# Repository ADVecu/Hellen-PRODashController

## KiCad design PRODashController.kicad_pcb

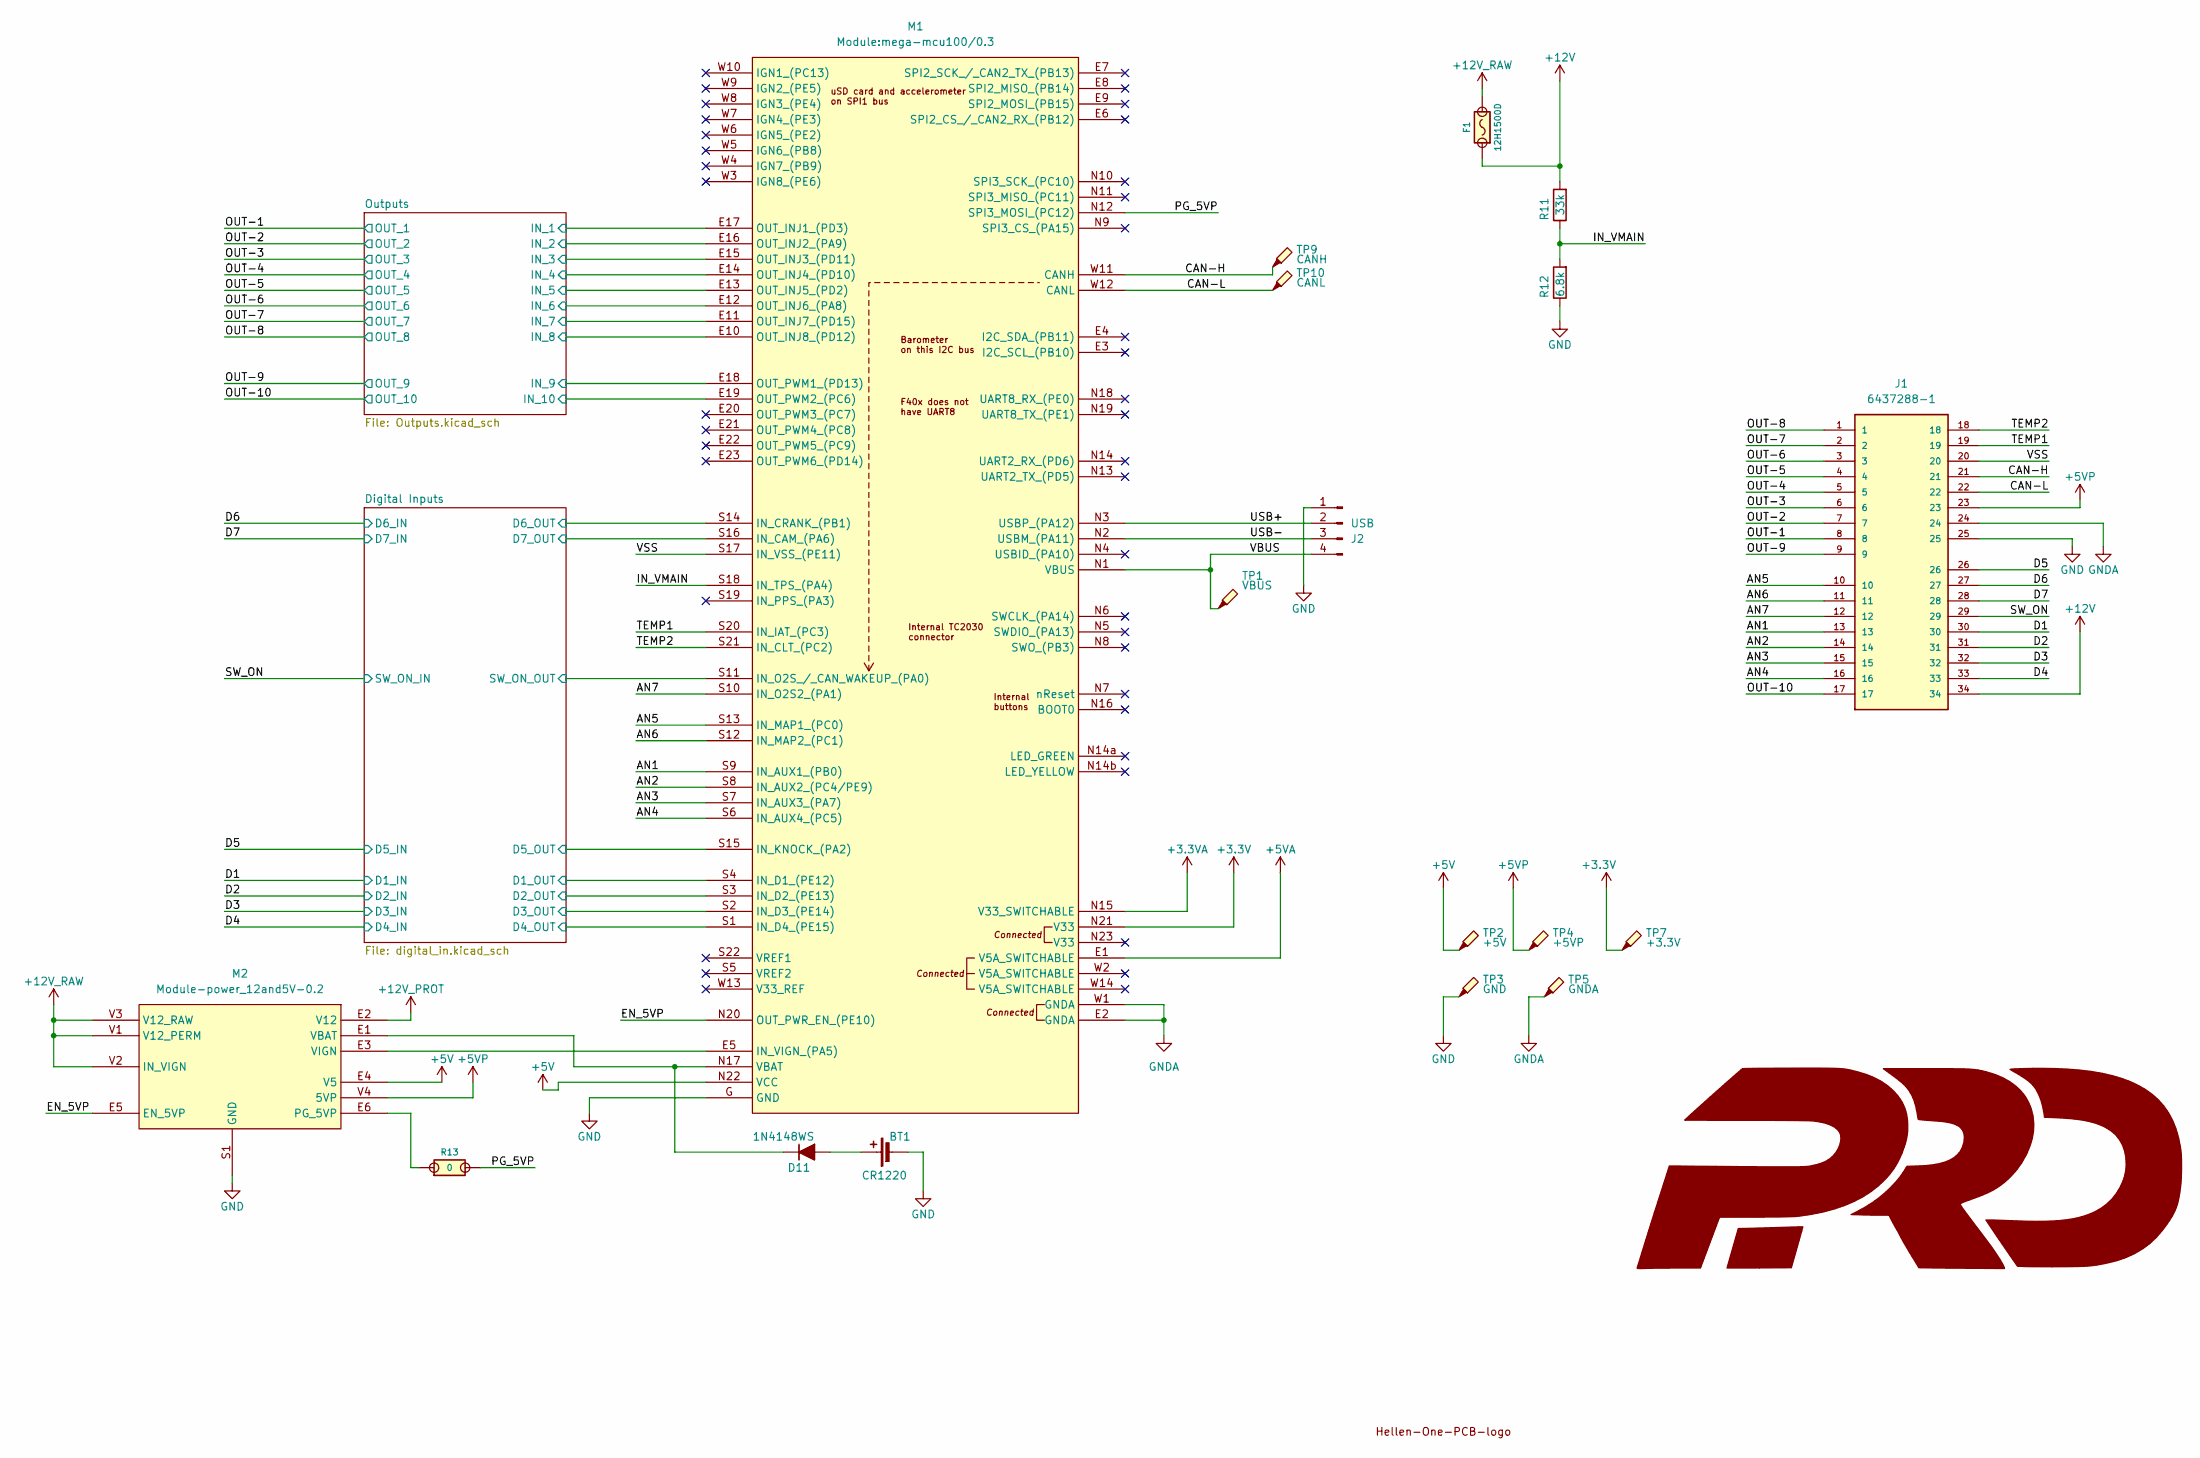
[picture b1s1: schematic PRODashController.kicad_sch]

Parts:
BT1: CR1220; CR1220-2; LCSC C70381
D11: 1N4148WS; SOD-323; LCSC C2128
F1: 12H1500D; PAD-1206-PAD; LCSC C182446
G1: LOGO
J1: 6437288-1; TE_6437288-1; PARTREV A1
J2: USB; JST_PH_B4B-PH-K_1x04_P2.00mm_Vertical; LCSC C5305780
M1: Module:mega-mcu100/0.3; mega-mcu100
M2: Module-power_12and5V-0.2; power_12and5V
R11: 33k; R0603; LCSC C4216
R12: 6.8k; R0603; LCSC C23212
R13: 0; R0805; LCSC C17477
TP1: VBUS; TestPoint_Pad_D1.0mm
TP2: +5V; TestPoint_Pad_D1.0mm
TP3: GND; TestPoint_Pad_D2.0mm
TP4: +5VP; TestPoint_Pad_D1.0mm
TP5: GNDA; TestPoint_Pad_D1.0mm
TP7: +3.3V; TestPoint_Pad_D1.0mm
TP9: CANH; TestPoint_Pad_D1.0mm
TP10: CANL; TestPoint_Pad_D1.0mm

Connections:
+3.3V: M1.N21 (V33), TP7.1
+3.3VA: M1.N15 (V33_SWITCHABLE)
+5V: M1.N22 (VCC), M2.E4 (V5), TP2.1
+5VA: M1.E1 (V5A_SWITCHABLE)
+5VP: J1.23, M2.V4 (5VP), TP4.1
+12V: F1.1, J1.34, R11.2
+12V_PROT: M2.E2 (V12); also elsewhere on the board
+12V_RAW: F1.2, M2.V1 (V12_PERM), M2.V2 (IN_VIGN), M2.V3 (V12_RAW); also elsewhere on the board
/AN1: J1.13, M1.S9 (IN_AUX1_(PB0))
/AN2: J1.14, M1.S8 (IN_AUX2_(PC4/PE9))
/AN3: J1.15, M1.S7 (IN_AUX3_(PA7))
/AN4: J1.16, M1.S6 (IN_AUX4_(PC5))
/AN5: J1.10, M1.S13 (IN_MAP1_(PC0))
/AN6: J1.11, M1.S12 (IN_MAP2_(PC1))
/AN7: J1.12, M1.S10 (IN_O2S2_(PA1))
/CAN-H: J1.21, M1.W11 (CANH), TP9.1
/CAN-L: J1.22, M1.W12 (CANL), TP10.1
/D1: J1.30; also elsewhere on the board
/D2: J1.31; also elsewhere on the board
/D3: J1.32; also elsewhere on the board
/D4: J1.33; also elsewhere on the board
/D5: J1.26; also elsewhere on the board
/D6: J1.27; also elsewhere on the board
/D7: J1.28; also elsewhere on the board
/Digital Inputs/D1_OUT: M1.S4 (IN_D1_(PE12)); also elsewhere on the board
/Digital Inputs/D2_OUT: M1.S3 (IN_D2_(PE13)); also elsewhere on the board
/Digital Inputs/D3_OUT: M1.S2 (IN_D3_(PE14)); also elsewhere on the board
/Digital Inputs/D4_OUT: M1.S1 (IN_D4_(PE15)); also elsewhere on the board
/Digital Inputs/D5_OUT: M1.S15 (IN_KNOCK_(PA2)); also elsewhere on the board
/Digital Inputs/D6_OUT: M1.S14 (IN_CRANK_(PB1)); also elsewhere on the board
/Digital Inputs/D7_OUT: M1.S16 (IN_CAM_(PA6)); also elsewhere on the board
/Digital Inputs/SW_ON_OUT: M1.S11 (IN_O2S_/_CAN_WAKEUP_(PA0)); also elsewhere on the board
/EN_5VP: M1.N20 (OUT_PWR_EN_(PE10)), M2.E5 (EN_5VP)
/IN_VMAIN: M1.S18 (IN_TPS_(PA4)), R11.1, R12.2
/OUT-1: J1.8; also elsewhere on the board
/OUT-2: J1.7; also elsewhere on the board
/OUT-3: J1.6; also elsewhere on the board
/OUT-4: J1.5; also elsewhere on the board
/OUT-5: J1.4; also elsewhere on the board
/OUT-6: J1.3; also elsewhere on the board
/OUT-7: J1.2; also elsewhere on the board
/OUT-8: J1.1; also elsewhere on the board
/OUT-9: J1.9; also elsewhere on the board
/OUT-10: J1.17; also elsewhere on the board
/Outputs/IN_1: M1.E17 (OUT_INJ1_(PD3)); also elsewhere on the board
/Outputs/IN_2: M1.E16 (OUT_INJ2_(PA9)); also elsewhere on the board
/Outputs/IN_3: M1.E15 (OUT_INJ3_(PD11)); also elsewhere on the board
/Outputs/IN_4: M1.E14 (OUT_INJ4_(PD10)); also elsewhere on the board
/Outputs/IN_5: M1.E13 (OUT_INJ5_(PD2)); also elsewhere on the board
/Outputs/IN_6: M1.E12 (OUT_INJ6_(PA8)); also elsewhere on the board
/Outputs/IN_7: M1.E11 (OUT_INJ7_(PD15)); also elsewhere on the board
/Outputs/IN_8: M1.E10 (OUT_INJ8_(PD12)); also elsewhere on the board
/Outputs/IN_9: M1.E18 (OUT_PWM1_(PD13)); also elsewhere on the board
/Outputs/IN_10: M1.E19 (OUT_PWM2_(PC6)); also elsewhere on the board
/PG_5VP: M1.N12 (SPI3_MOSI_(PC12)), R13.2
/SW_ON: J1.29; also elsewhere on the board
/TEMP1: J1.19, M1.S20 (IN_IAT_(PC3))
/TEMP2: J1.18, M1.S21 (IN_CLT_(PC2))
/USB+: J2.2, M1.N3 (USBP_(PA12))
/USB-: J2.3, M1.N2 (USBM_(PA11))
/VBUS: J2.4, M1.N1 (VBUS), TP1.1
/VSS: J1.20, M1.S17 (IN_VSS_(PE11))
GND: BT1.2 (-), J1.25, J2.1, M1.G (GND), M2.S1 (GND), R12.1, TP3.1; also elsewhere on the board
GNDA: J1.24, M1.E2 (GNDA), M1.W1 (GNDA), TP5.1
unnamed: BT1.1 (+), D11.2 (A)
unnamed: D11.1 (K), M1.N17 (VBAT), M2.E1 (VBAT)
unnamed: M1.E5 (IN_VIGN_(PA5)), M2.E3 (VIGN)
unnamed: M2.E6 (PG_5VP), R13.1

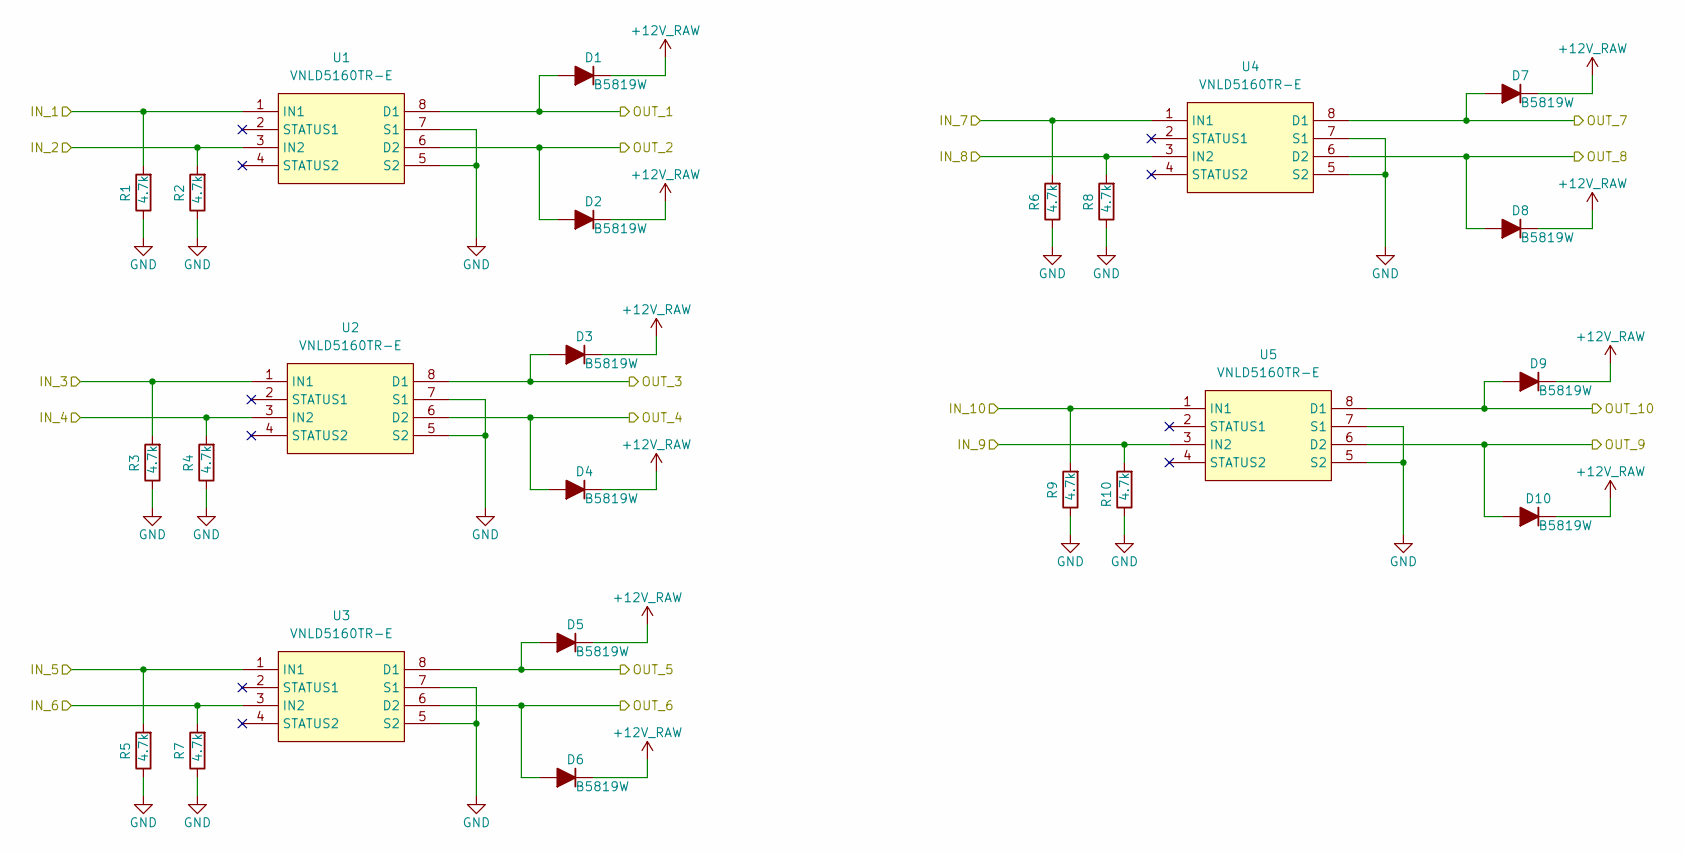
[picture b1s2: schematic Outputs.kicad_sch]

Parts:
D1, D2, D3, D4, D5, D6, D7, D8, D9, D10: B5819W; SOD-123; LCSC C8598
R1, R2, R3, R4, R5, R6, R7, R8, R9, R10: 4.7k; R0603; LCSC C23162
U1, U2, U3, U4, U5: VNLD5160TR-E; SOIC-8_3.9x4.9mm_P1.27mm; LCSC C377942

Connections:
+12V_RAW: D1.1 (K), D2.1 (K), D3.1 (K), D4.1 (K), D5.1 (K), D6.1 (K), D7.1 (K), D8.1 (K), D9.1 (K), D10.1 (K); also elsewhere on the board
/OUT-1: D1.2 (A), U1.8 (D1); also elsewhere on the board
/OUT-2: D2.2 (A), U1.6 (D2); also elsewhere on the board
/OUT-3: D3.2 (A), U2.8 (D1); also elsewhere on the board
/OUT-4: D4.2 (A), U2.6 (D2); also elsewhere on the board
/OUT-5: D5.2 (A), U3.8 (D1); also elsewhere on the board
/OUT-6: D6.2 (A), U3.6 (D2); also elsewhere on the board
/OUT-7: D7.2 (A), U4.8 (D1); also elsewhere on the board
/OUT-8: D8.2 (A), U4.6 (D2); also elsewhere on the board
/OUT-9: D10.2 (A), U5.6 (D2); also elsewhere on the board
/OUT-10: D9.2 (A), U5.8 (D1); also elsewhere on the board
/Outputs/IN_1: R1.2, U1.1 (IN1); also elsewhere on the board
/Outputs/IN_2: R2.2, U1.3 (IN2); also elsewhere on the board
/Outputs/IN_3: R3.2, U2.1 (IN1); also elsewhere on the board
/Outputs/IN_4: R4.2, U2.3 (IN2); also elsewhere on the board
/Outputs/IN_5: R5.2, U3.1 (IN1); also elsewhere on the board
/Outputs/IN_6: R7.2, U3.3 (IN2); also elsewhere on the board
/Outputs/IN_7: R6.2, U4.1 (IN1); also elsewhere on the board
/Outputs/IN_8: R8.2, U4.3 (IN2); also elsewhere on the board
/Outputs/IN_9: R10.2, U5.3 (IN2); also elsewhere on the board
/Outputs/IN_10: R9.2, U5.1 (IN1); also elsewhere on the board
GND: R1.1, R2.1, R3.1, R4.1, R5.1, R6.1, R7.1, R8.1, R9.1, R10.1, U1.5 (S2), U1.7 (S1), U2.5 (S2), U2.7 (S1), U3.5 (S2), U3.7 (S1), U4.5 (S2), U4.7 (S1), U5.5 (S2), U5.7 (S1); also elsewhere on the board

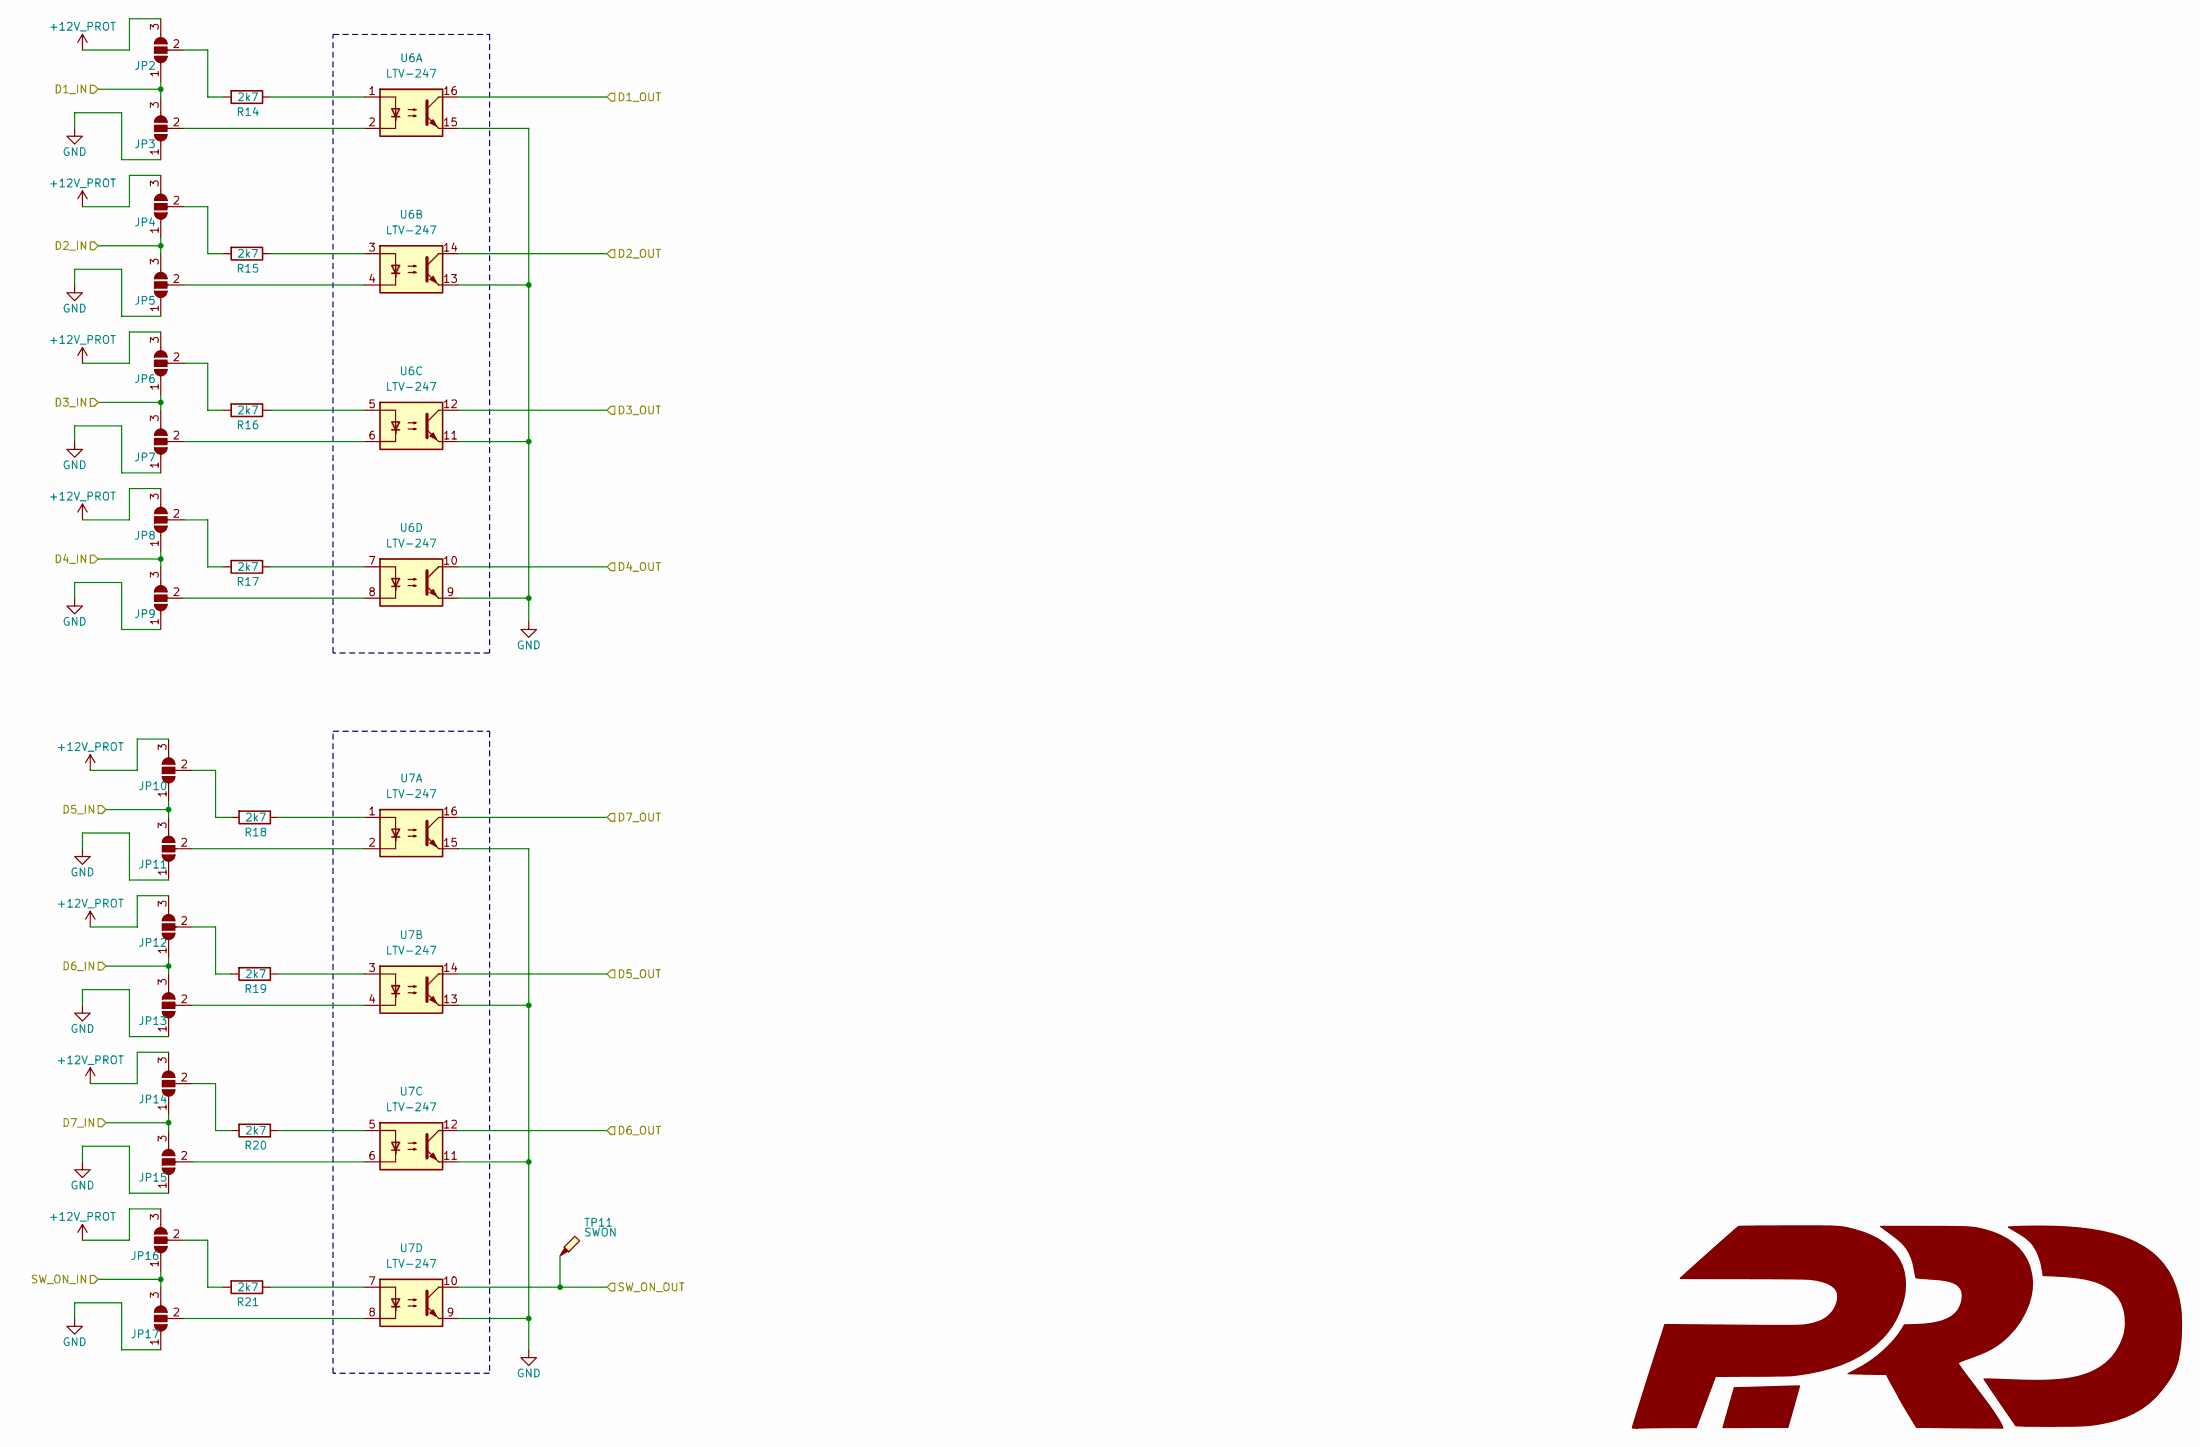
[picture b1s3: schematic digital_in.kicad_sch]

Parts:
JP2, JP3, JP4, JP5, JP6, JP7, JP8, JP9, JP10, JP11, JP12, JP13, JP14, JP15, JP16, JP17: SolderJumper_3_Open; SolderJumper-3_P1.3mm_Open_Pad1.0x1.5mm
R14, R15, R16, R17, R18, R19, R20, R21: 2k7; R0805; LCSC C17530
TP11: SWON; TestPoint_Pad_D1.0mm
U6, U7: LTV-247; SOP-16_4.4x10.4mm_P1.27mm; LCSC C115451

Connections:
+12V_PROT: JP2.3 (B), JP4.3 (B), JP6.3 (B), JP8.3 (B), JP10.3 (B), JP12.3 (B), JP14.3 (B), JP16.3 (B); also elsewhere on the board
/D1: JP2.1 (A), JP3.3 (B); also elsewhere on the board
/D2: JP4.1 (A), JP5.3 (B); also elsewhere on the board
/D3: JP6.1 (A), JP7.3 (B); also elsewhere on the board
/D4: JP8.1 (A), JP9.3 (B); also elsewhere on the board
/D5: JP10.1 (A), JP11.3 (B); also elsewhere on the board
/D6: JP12.1 (A), JP13.3 (B); also elsewhere on the board
/D7: JP14.1 (A), JP15.3 (B); also elsewhere on the board
/Digital Inputs/D1_OUT: U6.16; also elsewhere on the board
/Digital Inputs/D2_OUT: U6.14; also elsewhere on the board
/Digital Inputs/D3_OUT: U6.12; also elsewhere on the board
/Digital Inputs/D4_OUT: U6.10; also elsewhere on the board
/Digital Inputs/D5_OUT: U7.14; also elsewhere on the board
/Digital Inputs/D6_OUT: U7.12; also elsewhere on the board
/Digital Inputs/D7_OUT: U7.16; also elsewhere on the board
/Digital Inputs/SW_ON_OUT: TP11.1, U7.10; also elsewhere on the board
/SW_ON: JP16.1 (A), JP17.3 (B); also elsewhere on the board
GND: JP3.1 (A), JP5.1 (A), JP7.1 (A), JP9.1 (A), JP11.1 (A), JP13.1 (A), JP15.1 (A), JP17.1 (A), U6.9, U6.11, U6.13, U6.15, U7.9, U7.11, U7.13, U7.15; also elsewhere on the board
unnamed: JP2.2 (C), R14.2
unnamed: JP3.2 (C), U6.2
unnamed: JP4.2 (C), R15.2
unnamed: JP5.2 (C), U6.4
unnamed: JP6.2 (C), R16.2
unnamed: JP7.2 (C), U6.6
unnamed: JP8.2 (C), R17.2
unnamed: JP9.2 (C), U6.8
unnamed: JP10.2 (C), R18.2
unnamed: JP11.2 (C), U7.2
unnamed: JP12.2 (C), R19.2
unnamed: JP13.2 (C), U7.4
unnamed: JP14.2 (C), R20.2
unnamed: JP15.2 (C), U7.6
unnamed: JP16.2 (C), R21.2
unnamed: JP17.2 (C), U7.8
unnamed: R14.1, U6.1
unnamed: R15.1, U6.3
unnamed: R16.1, U6.5
unnamed: R17.1, U6.7
unnamed: R18.1, U7.1
unnamed: R19.1, U7.3
unnamed: R20.1, U7.5
unnamed: R21.1, U7.7

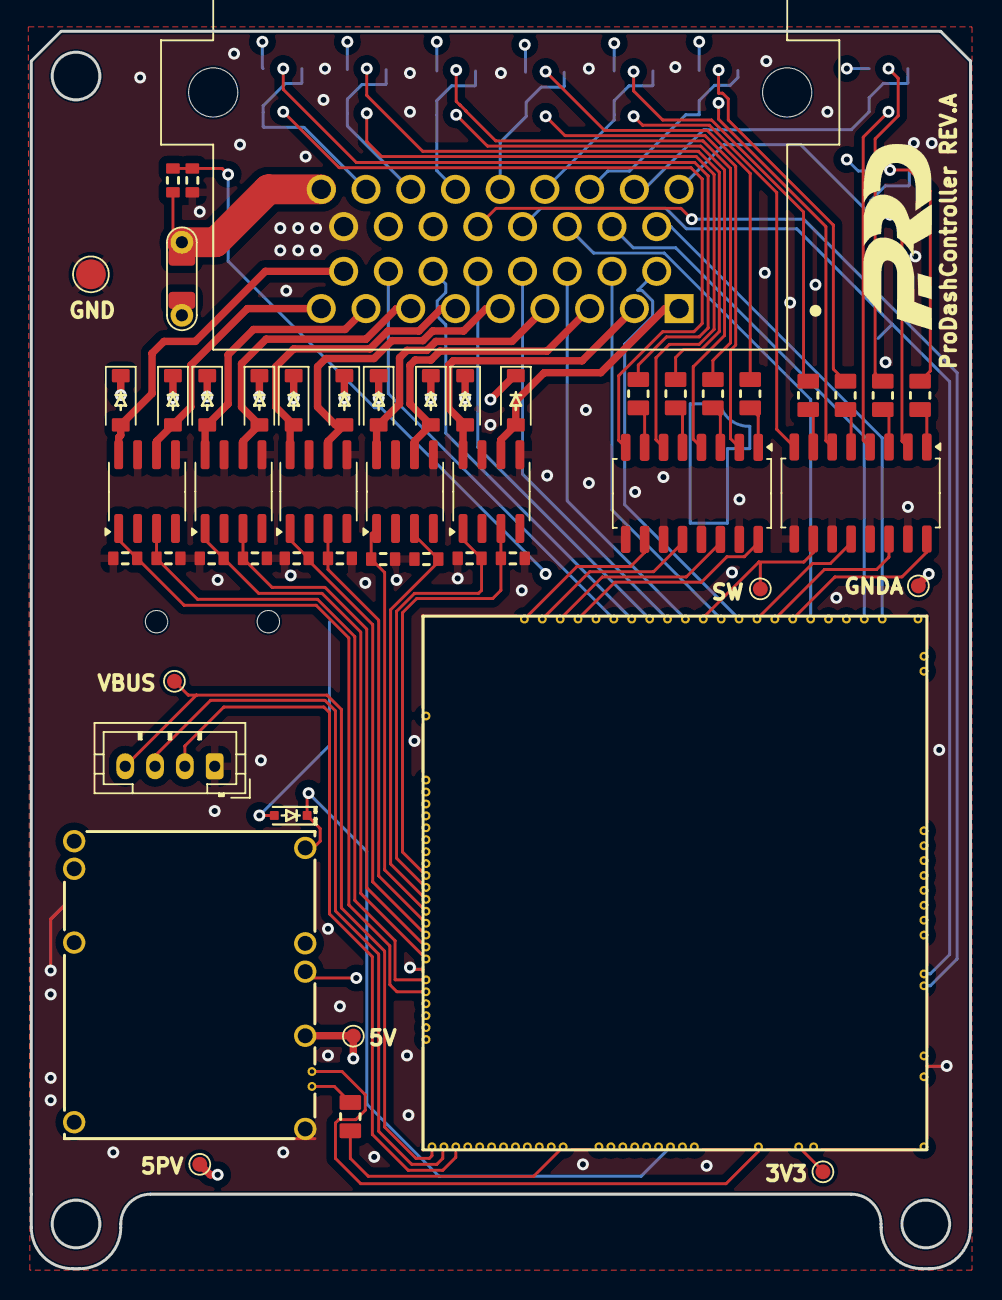
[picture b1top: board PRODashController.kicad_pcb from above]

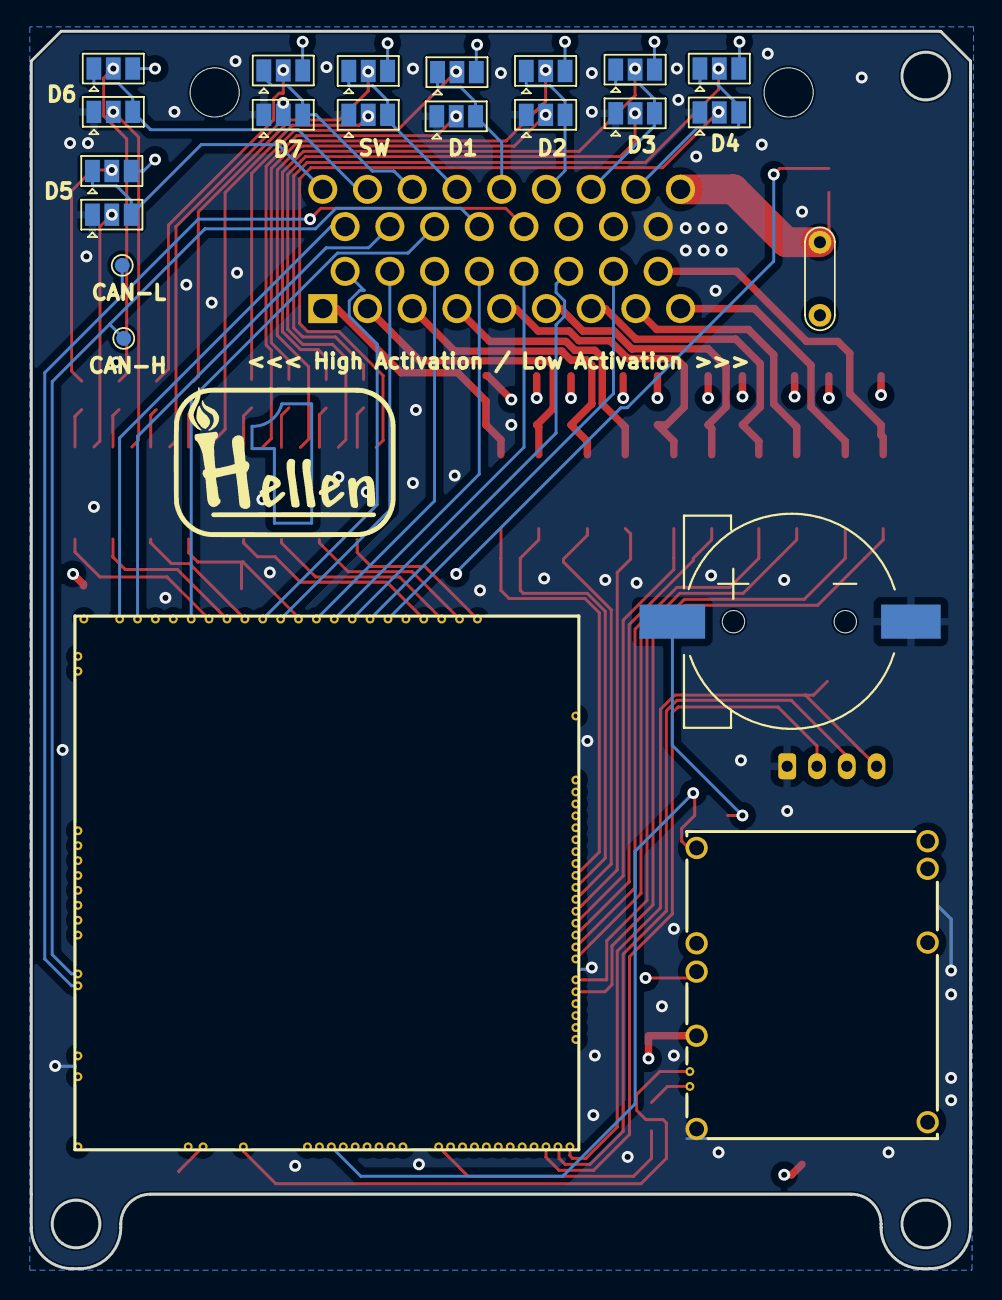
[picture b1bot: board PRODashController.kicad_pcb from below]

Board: 4 copper layers, 63.0 x 83.0 mm, 72 parts (20 on the bottom side), 90 nets.

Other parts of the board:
G2: LOGO; PRO_LOGO

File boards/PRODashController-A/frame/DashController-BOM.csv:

Comment,Designator,Footprint,LCSC Part #
"CR1220","BT1","CR1220-2","C70381"
"B5819W","D1","SOD-123","C8598"
"B5819W","D2","SOD-123","C8598"
"B5819W","D3","SOD-123","C8598"
"B5819W","D4","SOD-123","C8598"
"B5819W","D5","SOD-123","C8598"
"B5819W","D6","SOD-123","C8598"
"B5819W","D7","SOD-123","C8598"
"B5819W","D8","SOD-123","C8598"
"B5819W","D9","SOD-123","C8598"
"B5819W","D10","SOD-123","C8598"
"1N4148WS","D11","SOD-323","C2128"
"12H1500D","F1","PAD-1206-PAD","C182446"
"LOGO","G1","LOGO",""
"LOGO","G2","PRO_LOGO",""
"6437288-1","J1","TE_6437288-1",""
"USB","J2","JST_PH_B4B-PH-K_1x04_P2.00mm_Vertical","C5305780"
"Module:mega-mcu100/0.3","M1","mega-mcu100",""
"Module:power_12and5V/0.2","M2","power_12and5V",""
"4.7k","R1","R0603","C23162"
"4.7k","R2","R0603","C23162"
"4.7k","R3","R0603","C23162"
"4.7k","R4","R0603","C23162"
"4.7k","R5","R0603","C23162"
"4.7k","R6","R0603","C23162"
"4.7k","R7","R0603","C23162"
"4.7k","R8","R0603","C23162"
"4.7k","R9","R0603","C23162"
"4.7k","R10","R0603","C23162"
"33k","R11","R0603","C4216"
"6.8k","R12","R0603","C23212"
"0","R13","R0805","C17477"
"2k7","R14","R0805","C17530"
"2k7","R15","R0805","C17530"
"2k7","R16","R0805","C17530"
"2k7","R17","R0805","C17530"
"2k7","R18","R0805","C17530"
"2k7","R19","R0805","C17530"
"2k7","R20","R0805","C17530"
"2k7","R21","R0805","C17530"
"VBUS","TP1","TestPoint_Pad_D1.0mm",""
"+5V","TP2","TestPoint_Pad_D1.0mm",""
"GND","TP3","TestPoint_Pad_D2.0mm",""
"+5VP","TP4","TestPoint_Pad_D1.0mm",""
"GNDA","TP5","TestPoint_Pad_D1.0mm",""
"+3.3V","TP7","TestPoint_Pad_D1.0mm",""
"CANH","TP9","TestPoint_Pad_D1.0mm",""
"CANL","TP10","TestPoint_Pad_D1.0mm",""
"SWON","TP11","TestPoint_Pad_D1.0mm",""
"VNLD5160TR-E","U1","SO8","C377942"
"VNLD5160TR-E","U2","SO8","C377942"
"VNLD5160TR-E","U3","SO8","C377942"
"VNLD5160TR-E","U4","SO8","C377942"
"VNLD5160TR-E","U5","SO8","C377942"
"LTV-247","U6","SOP-16_4.4x10.4mm_P1.27mm","C115451"
"LTV-247","U7","SOP-16_4.4x10.4mm_P1.27mm","C115451"

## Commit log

2024-05-24 Rev A
2024-05-24 [skip actions] Auto-generated board v2.1
2024-05-25 GHA says update hellen-one
2024-06-02 GHA says update kicad6-libraries
2024-07-19 Rev A - New Bom-Remplase
2024-07-19 Rev A - Pull-Up/Downs
2024-07-19 Rev A - Fix Typo
